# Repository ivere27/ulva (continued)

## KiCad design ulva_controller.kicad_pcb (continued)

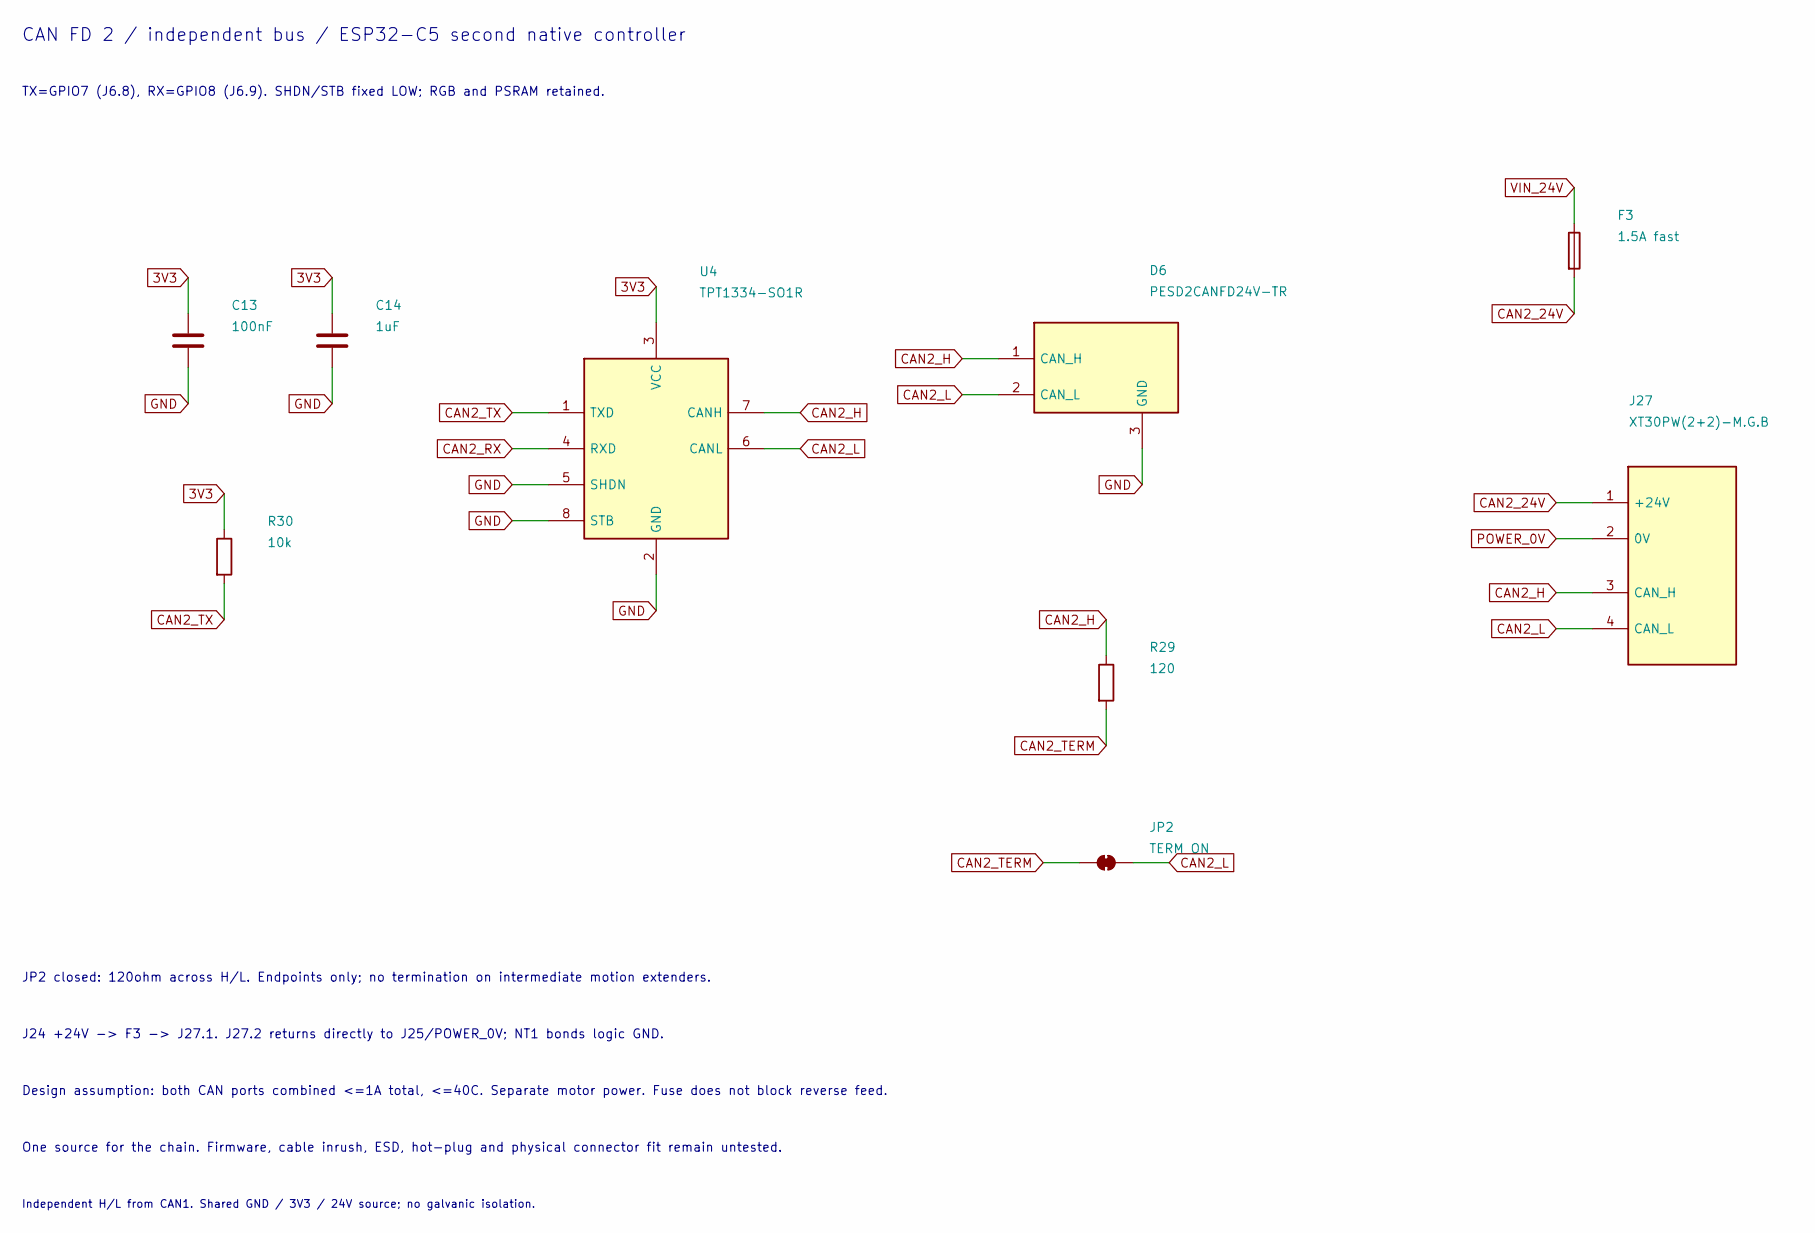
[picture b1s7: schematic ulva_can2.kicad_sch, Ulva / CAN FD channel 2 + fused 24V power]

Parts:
C13: 100nF; C_0603_1608Metric; MPN CC0603KRX7R9BB104; LCSC C14663
C14: 1uF; C_0603_1608Metric; MPN CL10A105KB8NNNC; LCSC C15849
D6: PESD2CANFD24V-TR; SOT-23; MPN PESD2CANFD24V-TR; LCSC C552486
F3: 1.5A fast; Fuse_Littelfuse_467_0603; MPN 046701.5NRHF; LCSC C187608
J27: XT30PW(2+2)-M.G.B; AMASS_XT30PW_2plus2_M_Horizontal; MPN XT30PW(2+2)-M.G.B; LCSC C19268030
JP2: TERM ON; SolderJumper-2_P1.3mm_Bridged_Pad1.0x1.5mm
R29: 120; R_1206_3216Metric; MPN 1206W4F1200T5E; LCSC C17909
R30: 10k; R_0603_1608Metric; MPN 0603WAF1002T5E; LCSC C25804
U4: TPT1334-SO1R; SOIC-8_3.9x4.9mm_P1.27mm; MPN TPT1334-SO1R; LCSC C44859616

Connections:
3V3: C13.1, C14.1, R30.1, U4.3 (VCC); also elsewhere on the board
CAN2_24V: F3.2, J27.1 (+24V)
CAN2_H: D6.1 (CAN_H), J27.3 (CAN_H), R29.1, U4.7 (CANH)
CAN2_L: D6.2 (CAN_L), J27.4 (CAN_L), JP2.2 (B), U4.6 (CANL)
CAN2_RX: U4.4 (RXD); also elsewhere on the board
CAN2_TERM: JP2.1 (A), R29.2
CAN2_TX: R30.2, U4.1 (TXD); also elsewhere on the board
GND: C13.2, C14.2, D6.3 (GND), U4.2 (GND), U4.5 (SHDN), U4.8 (STB); also elsewhere on the board
POWER_0V: J27.2 (0V); also elsewhere on the board
VIN_24V: F3.1; also elsewhere on the board

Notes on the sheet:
CAN FD 2 / independent bus / ESP32-C5 second native controller
TX=GPIO7 (J6.8), RX=GPIO8 (J6.9). SHDN/STB fixed LOW; RGB and PSRAM retained.
JP2 closed: 120ohm across H/L. Endpoints only; no termination on intermediate motion extenders.
J24 +24V -> F3 -> J27.1. J27.2 returns directly to J25/POWER_0V; NT1 bonds logic GND.
Design assumption: both CAN ports combined <=1A total, <=40C. Separate motor power. Fuse does not block reverse feed.
One source for the chain. Firmware, cable inrush, ESD, hot-plug and physical connector fit remain untested.
Independent H/L from CAN1. Shared GND / 3V3 / 24V source; no galvanic isolation.

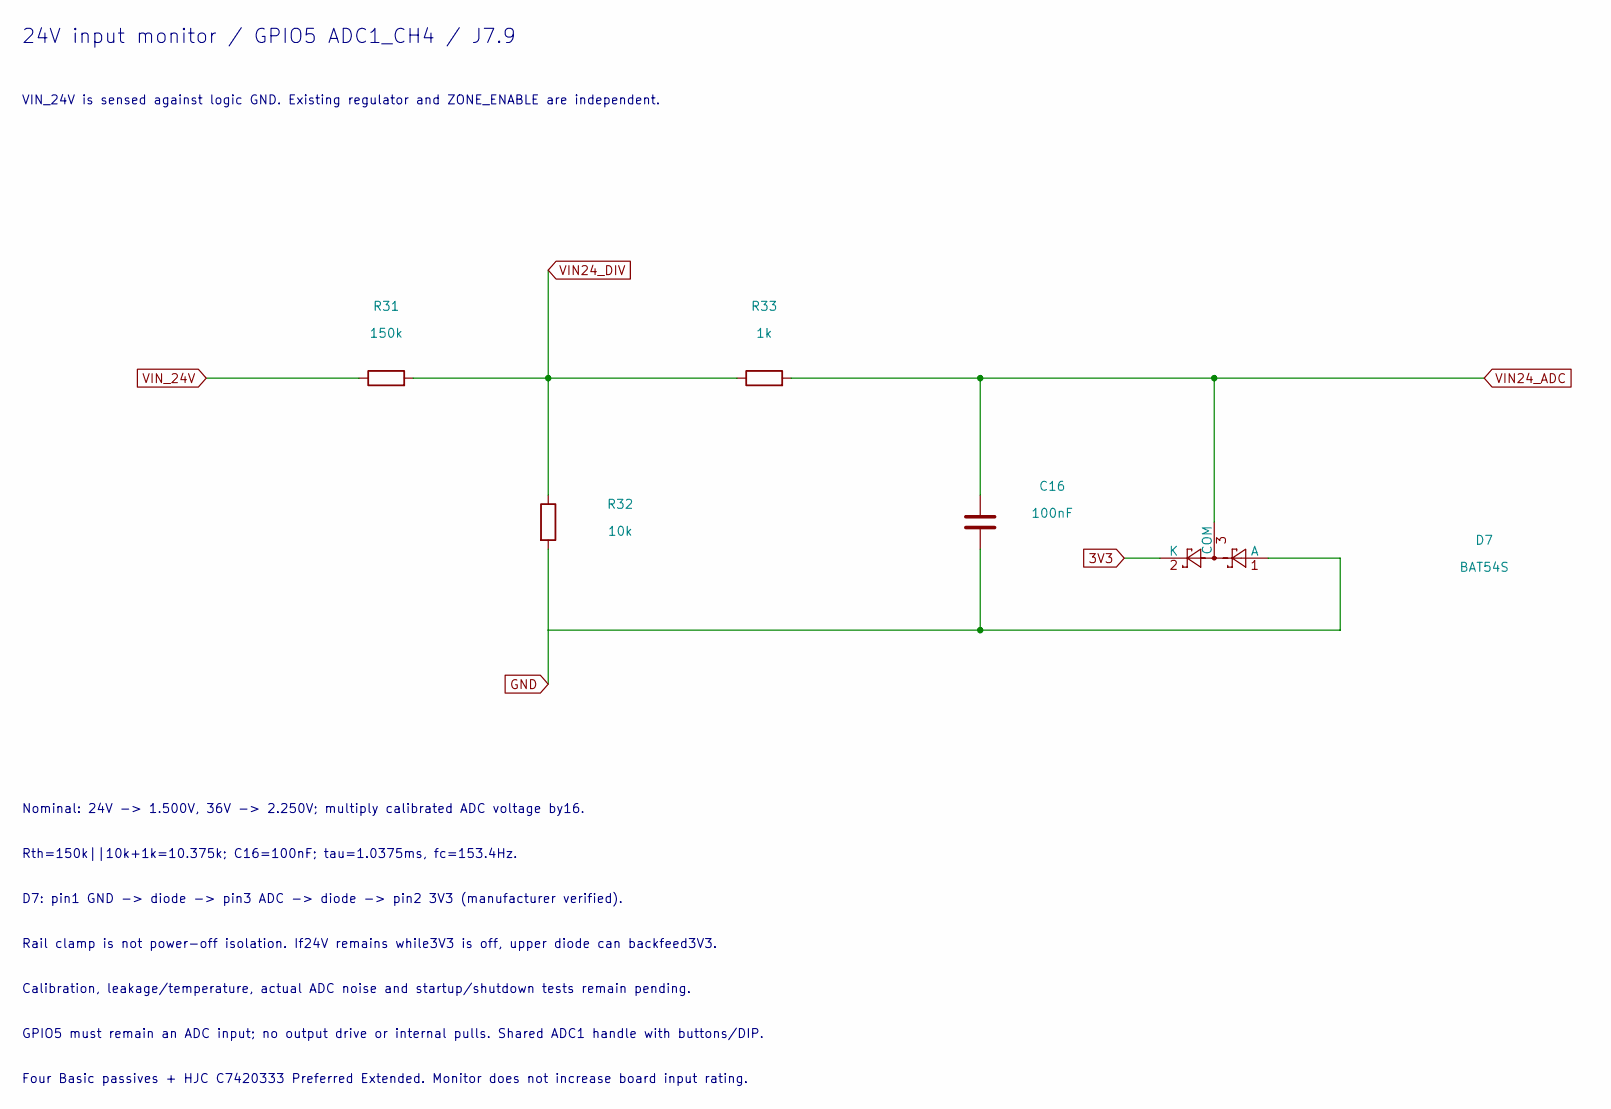
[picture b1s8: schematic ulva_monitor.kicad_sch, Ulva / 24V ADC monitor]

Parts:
C16: 100nF; C_0603_1608Metric; MPN CC0603KRX7R9BB104; LCSC C14663
D7: BAT54S; SOT-23; MPN BAT54S; LCSC C7420333
R31: 150k; R_0603_1608Metric; MPN 0603WAF1503T5E; LCSC C22807
R32: 10k; R_0603_1608Metric; MPN 0603WAF1002T5E; LCSC C25804
R33: 1k; R_0603_1608Metric; MPN 0603WAF1001T5E; LCSC C21190

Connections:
3V3: D7.2 (K); also elsewhere on the board
GND: C16.2, D7.1 (A), R32.2; also elsewhere on the board
VIN24_ADC: C16.1, D7.3 (COM), R33.2; also elsewhere on the board
VIN24_DIV: R31.2, R32.1, R33.1
VIN_24V: R31.1; also elsewhere on the board

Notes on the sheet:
24V input monitor / GPIO5 ADC1_CH4 / J7.9
VIN_24V is sensed against logic GND. Existing regulator and ZONE_ENABLE are independent.
Nominal: 24V -> 1.500V, 36V -> 2.250V; multiply calibrated ADC voltage by16.
Rth=150k||10k+1k=10.375k; C16=100nF; tau=1.0375ms, fc=153.4Hz.
D7: pin1 GND -> diode -> pin3 ADC -> diode -> pin2 3V3 (manufacturer verified).
Rail clamp is not power-off isolation. If24V remains while3V3 is off, upper diode can backfeed3V3.
Calibration, leakage/temperature, actual ADC noise and startup/shutdown tests remain pending.
GPIO5 must remain an ADC input; no output drive or internal pulls. Shared ADC1 handle with buttons/DIP.
Four Basic passives + HJC C7420333 Preferred Extended. Monitor does not increase board input rating.

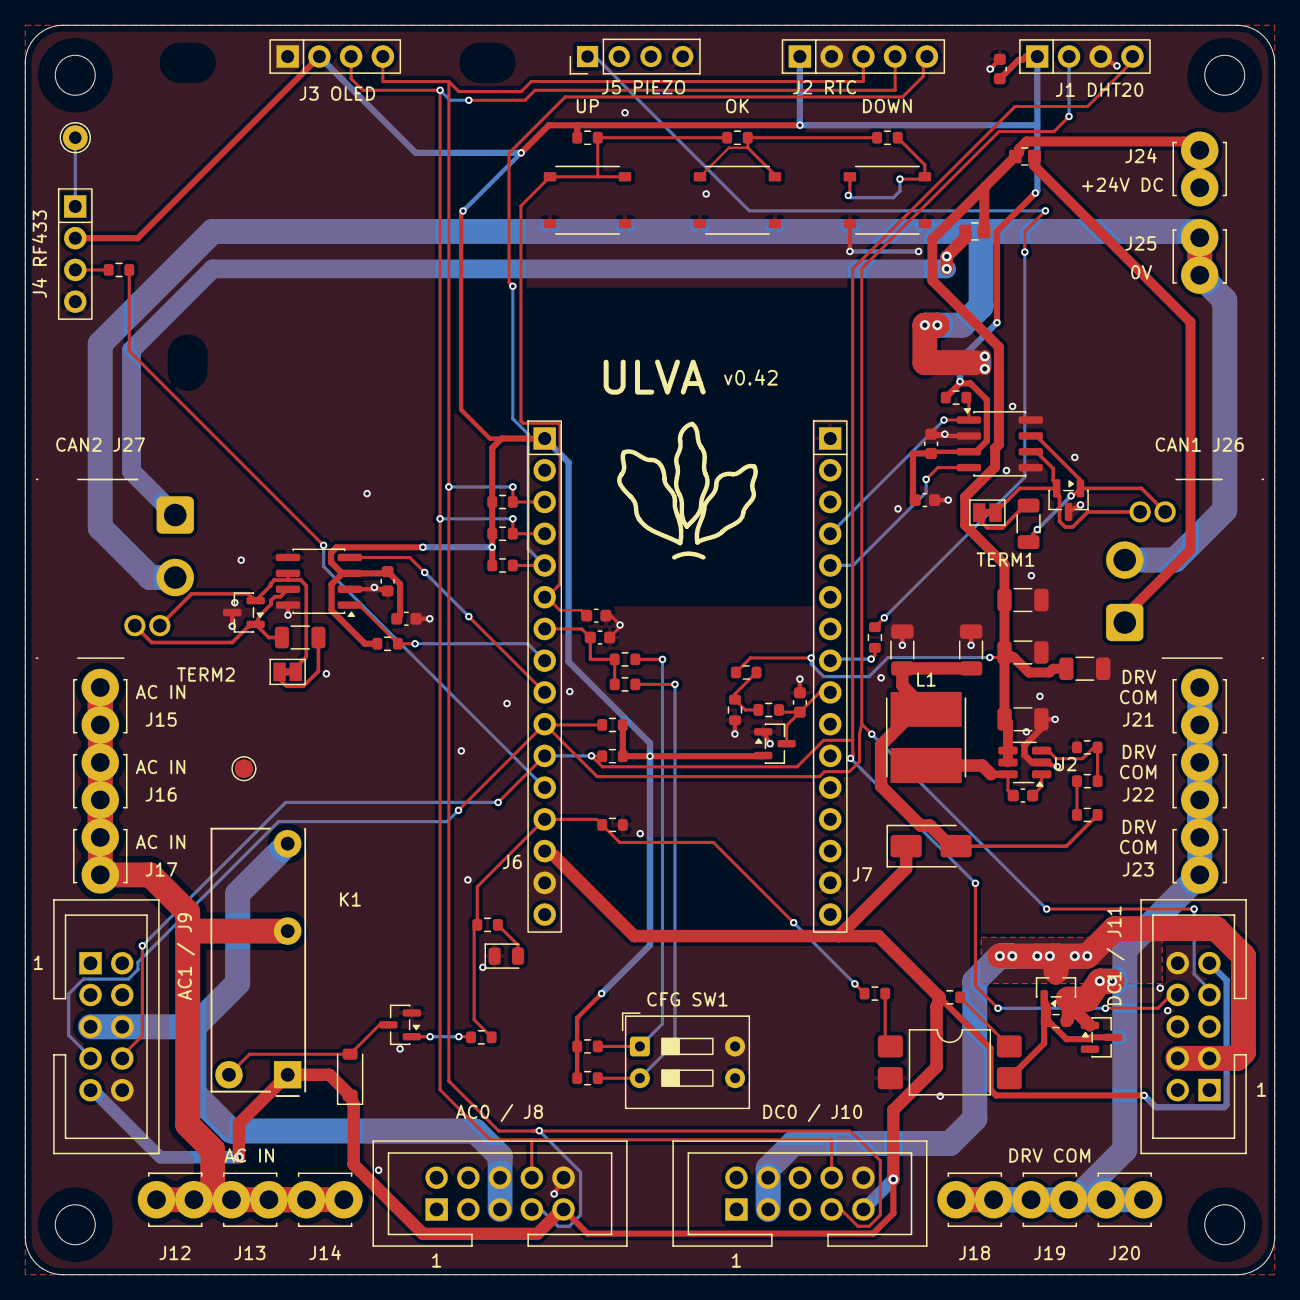
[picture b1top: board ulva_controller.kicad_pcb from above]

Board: 2 copper layers, 100.0 x 100.0 mm, 106 parts (0 on the bottom side), 51 nets.

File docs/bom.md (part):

# Bill of materials

The quantities below are for one **Ulva v0.42** carrier. The KiCad schematic
properties are the source of the part numbers; the PCB uses matching properties
and footprints. Plug-in modules, cables, mating connectors and mounting hardware
are additional items.

| Category | Quantity |
|---|---:|
| SMT parts tagged `JLC PCBA SMT` | 62 |
| Required manual SMT parts, U2 and L1 | 2 |
| Through-hole parts and antenna | 30 |
| PCB copper, holes, slots and test pad; no purchased component | 12 |
| **Total PCB footprints** | **106** |

There are **94 fitted parts** when fully populated. The tables record the design's
MPNs and LCSC numbers; they do not establish current stock, assembly availability
or library tier. A dash means that the corresponding sourcing field is not
recorded. See the [hardware reference](hardware.md) for wiring and power limits.

## SMT assembly candidates

These 62 parts carry the `JLC PCBA SMT` tag and are placed on the front side.
They form **26 part groups**, grouped by MPN, manufacturer, LCSC number and
footprint. The footprint column omits the KiCad library prefix.

| References | Qty | Value | Footprint | MPN | Manufacturer | LCSC |
|---|---:|---|---|---|---|---|
| C1, C5, C10, C12, C13, C15, C16 | 7 | 100nF; C5 explicitly marked 50V | `C_0603_1608Metric` | `CC0603KRX7R9BB104` | YAGEO | [C14663](https://www.lcsc.com/product-detail/C14663.html) |
| C3, C4, C8, C9 | 4 | 2.2uF / 50V | `C_1206_3216Metric` | `CL31B225KBHNNNE` | Samsung Electro-Mechanics | [C50254](https://www.lcsc.com/product-detail/C50254.html) |
| C6, C7 | 2 | 47uF / 10V | `C_1206_3216Metric` | `CL31A476MPHNNNE` | Samsung Electro-Mechanics | [C96123](https://www.lcsc.com/product-detail/C96123.html) |
| C11, C14 | 2 | 1uF | `C_0603_1608Metric` | `CL10A105KB8NNNC` | Samsung Electro-Mechanics | [C15849](https://www.lcsc.com/product-detail/C15849.html) |
| D1 | 1 | ZONE_ENABLE GREEN | `LED_0805_2012Metric` | `KT-0805G` | Hubei KENTO Elec | [C2297](https://www.lcsc.com/product-detail/C2297.html) |
| D2 | 1 | BZX84C8V2 | `SOT-23` | `BZX84C8V2` | hongjiacheng | [C22395522](https://www.lcsc.com/product-detail/C22395522.html) |
| D3 | 1 | 1N4148W | `D_SOD-123` | `1N4148W` | ST(Semtech) | [C81598](https://www.lcsc.com/product-detail/C81598.html) |
| D4 | 1 | SS34 | `D_SMA` | `SS34` | MDD | [C8678](https://www.lcsc.com/product-detail/C8678.html) |
| D5, D6 | 2 | PESD2CANFD24V-TR | `SOT-23` | `PESD2CANFD24V-TR` | Nexperia | [C552486](https://www.lcsc.com/product-detail/C552486.html) |
| D7 | 1 | BAT54S | `SOT-23` | `BAT54S` | hongjiacheng | [C7420333](https://www.lcsc.com/product-detail/C7420333.html) |
| F2, F3 | 2 | 1.5A fast | `Fuse_Littelfuse_467_0603` | `046701.5NRHF` | Littelfuse | [C187608](https://www.lcsc.com/product-detail/C187608.html) |
| Q1, Q2 | 2 | AO3400A | `SOT-23` | `AO3400A` | AOS | [C20917](https://www.lcsc.com/product-detail/C20917.html) |
| R1, R2, R3, R4, R13 | 5 | 4.7k | `R_0603_1608Metric` | `0603WAF4701T5E` | UNI-ROYAL | [C23162](https://www.lcsc.com/product-detail/C23162.html) |
| R5, R6, R11, R17, R26, R33 | 6 | 1k | `R_0603_1608Metric` | `0603WAF1001T5E` | UNI-ROYAL | [C21190](https://www.lcsc.com/product-detail/C21190.html) |
| R8, R12, R14, R15, R19, R23, R25, R27, R30, R32 | 10 | 10k | `R_0603_1608Metric` | `0603WAF1002T5E` | UNI-ROYAL | [C25804](https://www.lcsc.com/product-detail/C25804.html) |
| R16 | 1 | 2.2k | `R_0603_1608Metric` | `0603WAF2201T5E` | UNI-ROYAL | [C4190](https://www.lcsc.com/product-detail/C4190.html) |
| R18 | 1 | 330 | `R_0603_1608Metric` | `0603WAF3300T5E` | UNI-ROYAL | [C23138](https://www.lcsc.com/product-detail/C23138.html) |
| R20 | 1 | 47k | `R_0603_1608Metric` | `0603WAF4702T5E` | UNI-ROYAL | [C25819](https://www.lcsc.com/product-detail/C25819.html) |
| R21 | 1 | 51k | `R_0603_1608Metric` | `0603WAF5102T5E` | UNI-ROYAL | [C23196](https://www.lcsc.com/product-detail/C23196.html) |
| R22 | 1 | 2.7k | `R_0603_1608Metric` | `0603WAF2701T5E` | UNI-ROYAL | [C13167](https://www.lcsc.com/product-detail/C13167.html) |
| R24, R29 | 2 | 120 | `R_1206_3216Metric` | `1206W4F1200T5E` | UNI-ROYAL | [C17909](https://www.lcsc.com/product-detail/C17909.html) |
| R28 | 1 | 20k | `R_0603_1608Metric` | `0603WAF2002T5E` | UNI-ROYAL | [C4184](https://www.lcsc.com/product-detail/C4184.html) |
| R31 | 1 | 150k | `R_0603_1608Metric` | `0603WAF1503T5E` | UNI-ROYAL | [C22807](https://www.lcsc.com/product-detail/C22807.html) |
| SW2, SW3, SW4 | 3 | TS-1187A-B-A-B | `SW_XKB_TS-1187A_5.1x5.1mm` | `TS-1187A-B-A-B` | XKB Connection | [C318884](https://www.lcsc.com/product-detail/C318884.html) |
| U1 | 1 | LTV-817S-TA1-C | `SMDIP-4_W9.53mm` | `LTV-817S-TA1-C` | Lite-On | [C109227](https://www.lcsc.com/product-detail/C109227.html) |
| U3, U4 | 2 | TPT1334-SO1R | `SOIC-8_3.9x4.9mm_P1.27mm` | `TPT1334-SO1R` | 3PEAK | [C44859616](https://www.lcsc.com/product-detail/C44859616.html) |

## Manual assembly

U2 and L1 are required SMT parts tagged `Manual SMT`:

| References | Qty | Value | Footprint | MPN | Manufacturer | LCSC |
|---|---:|---|---|---|---|---|
| U2 | 1 | SY8301ABC | `SOT-23-6_Handsoldering` | `SY8301ABC` | Silergy | [C2927130](https://www.lcsc.com/product-detail/C2927130.html) |
| L1 | 1 | 4.7uH | `L_Sunlord_SWPA6045_6x6mm` | `SWPA6045S4R7MT` | Sunlord | [C78804](https://www.lcsc.com/product-detail/C78804.html) |

The following 30 parts use through-hole assembly. Only some carry an explicit
`Manual THT` tag; an empty assembly field does not make a part an SMT candidate.

| References | Qty | Use / value | Footprint | MPN | Manufacturer | LCSC |
|---|---:|---|---|---|---|---|
| J1, J3, J4 | 3 | DHT20, OLED and RF433 module sockets | `Samtec_SSW-104-01-G-S_1x04_P2.54mm` | `SSW-104-01-G-S` | — | — |
| J2 | 1 | DS3231 RTC socket | `Samtec_SSW-105-01-G-S_1x05_P2.54mm` | `SSW-105-01-G-S` | — | — |
| J5 | 1 | Passive piezo header; pins 1 and 4 used | `PinHeader_1x04_P2.54mm_Vertical` | — | — | — |
| J6, J7 | 2 | ESP32-C5-DevKitC-1 v1.2 sockets | `Samtec_SSW-116-01-G-S_1x16_P2.54mm` | `SSW-116-01-G-S` | — | — |
| J8, J9, J10, J11 | 4 | AC0, AC1, DC0 and DC1 expansion headers | `ZHOURI_DC3-2.54-10PAS_IDC_2x05_P2.54mm` | `DC3-2.54-10PAS` | — | [C2977596](https://www.lcsc.com/product-detail/C2977596.html) |
| J12, J13, J14, J15, J16, J17 | 6 | Six parallel AC2_IN terminals | `TerminalBlock_MetzConnect_360272_1x01_Horizontal_ScrewM2.6` | `360272` | — | — |
| J18, J19, J20, J21, J22, J23 | 6 | Six parallel DRIVER COM terminals | `TerminalBlock_MetzConnect_360272_1x01_Horizontal_ScrewM2.6` | `360272` | METZ CONNECT | — |
| J24, J25 | 2 | 24 V DC input positive / POWER_0V | `TerminalBlock_MetzConnect_360272_1x01_Horizontal_ScrewM2.6` | `360272` | METZ CONNECT | — |
| J26, J27 | 2 | CAN1 / CAN2 power and data | `AMASS_XT30PW_2plus2_M_Horizontal` | `XT30PW(2+2)-M.G.B` | AMASS | [C19268030](https://www.lcsc.com/product-detail/C19268030.html) |
| K1 | 1 | HF46F/5-HS1 relay | `Relay_SPST_Hongfa_HF46F_HS1` | `HF46F/5-HS1` | — | — |
| SW1 | 1 | 206-2ST configuration DIP switch | `SW_DIP_SPSTx02_Slide_9.78x7.26mm_W7.62mm_P2.54mm` | `206-2ST` | — | — |
| AE1 | 1 | 433 MHz wire / spring antenna | `TestPoint_THTPad_D2.0mm_Drill1.0mm` | — | — | — |

J1–J4 and J6/J7 specify Samtec SSW sockets; J12–J25 specify METZ CONNECT
360272 terminals; K1 specifies Hongfa HF46F/5-HS1 and SW1 specifies CTS 206-2ST.
Some manufacturer fields are empty in the source, as shown above. No alternate
LCSC part is approved by this table: matching pitch or a similar product name
alone does not establish footprint or electrical compatibility.

## Board features

These 12 footprints do not require purchased components:

| References | Qty | Feature | Footprint |
|---|---:|---|---|
| JP1, JP2 | 2 | Normally closed CAN termination copper bridges | `SolderJumper-2_P1.3mm_Bridged_Pad1.0x1.5mm` |
| NT1 | 1 | POWER_0V to GND copper bond | `NetTie-2_SMD_Pad2.0mm` |
| H1, H2, H3, H4 | 4 | M3 mounting holes | `MountingHole_3.2mm_M3` |
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
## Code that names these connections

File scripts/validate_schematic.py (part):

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value("C1", "100nF")

# Official ESP32-C5-DevKitC-1 v1.2 PSRAM header numbers, J1/J3.
# Bus0 uses LP-I2C fixed GPIO2/3; bus1 uses HP-I2C GPIO9/10. GPIO15 is unavailable with PSRAM.
mapping(
    "J6",
    {
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    "GPIO11 remains unused by the carrier for DevKit UART TX",
)
mapping("TP2", {1: "GND"})
mapping("J5", {1: "UI_PIEZO", 4: "GND"})
nc("J5", 2)
nc("J5", 3)
mapping("R26", {1: "UI_PIEZO_PWM", 2: "UI_PIEZO"})
value("R26", "1k")
require(
    components["J5"].findtext("footprint")
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        and components[rr].findtext("./fields/field[@name='LCSC']") == lcsc,
        rr + ": button ladder uses the specified 1% 0603 part",
    )
mapping("C15", {1: "UI_BUTTON_ADC", 2: "GND"})
value("C15", "100nF")
require(
    components["C15"].findtext("footprint") == "Capacitor_SMD:C_0603_1608Metric"
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        == "Basic",
        rr + ": specified 1% Basic resistor for the 24V monitor",
    )
mapping("C16", {1: "VIN24_ADC", 2: "GND"})
value("C16", "100nF")
require(
    components["C16"].findtext("footprint") == "Capacitor_SMD:C_0603_1608Metric"
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    and components["C16"].findtext("./fields/field[@name='LCSC']") == "C14663",
    "C16: X7R 50V storage/filter capacitor on the protected ADC node",
)
mapping("D7", {1: "GND", 2: "3V3", 3: "VIN24_ADC"})
value("D7", "BAT54S")
require(
    components["D7"].findtext("footprint") == "Package_TO_SOT_SMD:SOT-23"
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)

# Boot configuration: two independent SPST contacts, pairs 1-4 and 2-3.
mapping("SW1", {1: "CFG_SW1_N", 2: "CFG_SW2_N", 3: "GND", 4: "GND"})
config_symbol = components["SW1"].find("libsource")
require(
    config_symbol is not None
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    signal = f"CFG_SW{i}_N"
    mapping(pull, {1: "3V3", 2: signal})
    value(pull, "1k")
    mapping(weight, {1: signal, 2: "CFG_ADC"})
    value(weight, resistance)
    require(
        {pin for pin, code in net_by_pin.items() if names[code] == signal}
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            == expected_lcsc,
            rr + ": selected 1% 0603 resistor and matching BOM number",
        )
mapping("C12", {1: "CFG_ADC", 2: "GND"})
value("C12", "100nF")
require(
    components["C12"].findtext("footprint") == "Capacitor_SMD:C_0603_1608Metric"
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    "C12 uses the existing 100nF X7R 50V 0603 capacitor",
)
require(
    {pin for pin, code in net_by_pin.items() if names[code] == "CFG_ADC"}
    == {("J6", "7"), ("R27", "2"), ("R28", "2"), ("C12", "1")},
    "Only GPIO6 ADC1_CH5 reads the weighted DIP voltage; no direct switch or supply bypass",
)
require(
    not {"CFG0_N", "CFG1_N"} & set(names.values()),
    "DIP switches do not use separate GPIO input nets",
)
# RTC alarm and RF receiver have independent GPIOs; no selection links.
mapping("R8", {1: "3V3", 2: "RTC_INT_N"})
value("R8", "10k")
mapping("J2", {5: "RTC_INT_N"})
mapping("R11", {1: "RF433_DO", 2: "RF433_RX"})
value("R11", "1k")
for ref in ("J4", "AE1", "R11"):
    require(
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    )
require(
    not {"CFG2_N", "CFG3_N", "GPIO23_IN"} & set(names.values()),
    "No unsupported DIP or shared GPIO23 nets",
)
for name, expected in {
    "RTC_INT_N": {("J6", "5"), ("J2", "5"), ("R8", "2")},
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# netlist can verify the relay path, but not the installed source or fuse.
for ref in ("J15", "J12", "J16", "J17", "J13", "J14"):
    require(ref in components, f"Required AC screw terminal {ref} is missing")
    mapping(ref, {1: "AC2_IN"})
    require(
        {pin for rr, pin in net_by_pin if rr == ref} == {"1"},
        f"{ref} must have exactly one electrical terminal",
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        == "TerminalBlock_MetzConnect:TerminalBlock_MetzConnect_360272_1x01_Horizontal_ScrewM2.6",
        f"{ref} must use the selected single-position METZ CONNECT footprint",
    )
mapping("K1", {"A1": "EXP_5V", "A2": "AC_RELAY_LOW", "13": "AC2_IN", "14": "EACRET"})
value("K1", "HF46F/5-HS1")
require(
    components["K1"].findtext("footprint") == "Ulva:Relay_SPST_Hongfa_HF46F_HS1",
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    "K1 symbol must represent a normally-open SPST mechanical contact",
)
require(
    {pin for pin, code in net_by_pin.items() if names[code] == "AC2_IN"}
    == {(r, "1") for r in ("J15", "J12", "J16", "J17", "J13", "J14")} | {("K1", "13")},
    "Externally fused transformer wire2 reaches only J15.1/J12.1 and the K1 contact input",
)
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    ("J9", "I2C1", True),
    ("J11", "I2C1", False),
]:
    mapping(ref, {7: prefix + "_SDA", 8: prefix + "_SCL", 9: "EXP_5V", 10: "GND"})
    for p in (5, 6) if ac else (3, 4):
        mapping(ref, {p: "EACRET" if ac else "DC_ZONE_RETURN"})
    for p in (1, 2, 3, 4) if ac else (1, 2, 5, 6):
        nc(ref, p)
require(
    {pin for pin, code in net_by_pin.items() if names[code] == "EACRET"}
    == {("K1", "14"), ("J8", "5"), ("J8", "6"), ("J9", "5"), ("J9", "6")},
    "EACRET connects only K1 and AC return pins; no added ground bond",
)
require(
    {pin for pin, code in net_by_pin.items() if names[code] == "DC_ZONE_RETURN"}
    == {("Q2", "3"), ("J10", "3"), ("J10", "4"), ("J11", "3"), ("J11", "4")},
    "DC_ZONE_RETURN connects only Q2 drain and DC return pins; no added ground bond",
)
require(
    len({net_by_pin[("J8", "5")], net_by_pin[("J10", "3")], net_by_pin[("J8", "10")]})
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    and net_by_pin[("J8", "8")] != net_by_pin[("J9", "8")],
    "I2C0 and I2C1 (HP) expansion buses remain electrically separate",
)
# GPIO25 drives both fail-off paths. The AC MOSFET sinks the relay coil current;
# the optocoupler operates a board-5V-powered, single-MOSFET DC command-return cut.
mapping("Q1", {1: "AC_RELAY_GATE", 2: "GND", 3: "AC_RELAY_LOW"})
value("Q1", "AO3400A")
require(
    components["Q1"].findtext("footprint") == "Package_TO_SOT_SMD:SOT-23",
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    components["Q1"].findtext("./fields/field[@name='MPN']") == "AO3400A",
    "Q1 must use the specified logic-level coil driver",
)
mapping("R17", {1: "ZONE_ENABLE", 2: "AC_RELAY_GATE"})
value("R17", "1k")
mapping("R15", {1: "ZONE_ENABLE", 2: "GND"})
value("R15", "10k")
mapping("D3", {1: "EXP_5V", 2: "AC_RELAY_LOW"})
value("D3", "1N4148W")
require(
    components["D3"].findtext("footprint") == "Diode_SMD:D_SOD-123",
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    "D3 must use the specified coil-flyback diode",
)
require(
    {pin for pin, code in net_by_pin.items() if names[code] == "AC_RELAY_LOW"}
    == {("K1", "A2"), ("Q1", "3"), ("D3", "2")},
    "Relay coil low side reaches only the MOSFET drain and flyback diode anode",
)
require(
    {pin for pin, code in net_by_pin.items() if names[code] == "AC_RELAY_GATE"}
    == {("Q1", "1"), ("R17", "2")},
    "Relay gate reaches the shared R15 pull-down through R17",
)

for ref in ("J18", "J19", "J20", "J21", "J22", "J23"):
    mapping(ref, {1: "DC_DRIVER_COM"})
    require(
        components[ref].findtext("footprint")
        == components["J25"].findtext("footprint"),
        ref + " uses the selected COM terminal",
    )
mapping("J25", {1: "POWER_0V"})
require(
    {pin for rr, pin in net_by_pin if rr == "J25"} == {"1"},
    "J25 has only the supply-negative pin",
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    components["J25"].findtext("./fields/field[@name='MPN']") == "360272",
    "J25 uses METZ CONNECT 360272",
)
mapping("R18", {1: "ZONE_ENABLE", 2: "DC_LED_A"})
value("R18", "330")
mapping("U1", {1: "DC_LED_A", 2: "GND", 3: "DC_GATE", 4: "DC_OPTO_C"})
value("U1", "LTV-817S-TA1-C")
require(
    components["U1"].findtext("footprint") == "Package_DIP:SMDIP-4_W9.53mm",
    "U1 must use the selected gull-wing SMDIP-4 footprint",
)
mapping("Q2", {1: "DC_GATE", 2: "DC_DRIVER_COM", 3: "DC_ZONE_RETURN"})
value("Q2", "AO3400A")
require(
    components["Q2"].findtext("footprint") == "Package_TO_SOT_SMD:SOT-23",
    "Q2 must use the selected AO3400A SOT-23 footprint",
)
mapping("D2", {1: "DC_DRIVER_COM", 3: "DC_GATE"})
nc("D2", 2)
value("D2", "BZX84C8V2")
for field, expected in {
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        components["D2"].findtext(f"./fields/field[@name='{field}']") == expected,
        f"D2 {field} must match the selected C22395522, independently of Q2",
    )
mapping("R19", {1: "EXP_5V", 2: "DC_OPTO_C"})
value("R19", "10k")
mapping("R20", {1: "DC_GATE", 2: "DC_DRIVER_COM"})
value("R20", "47k")
require(
    {pin for pin, code in net_by_pin.items() if names[code] == "DC_DRIVER_COM"}
    == {(r, "1") for r in ("J18", "J19", "J20", "J21", "J22", "J23")}
    | {("Q2", "2"), ("R20", "2"), ("D2", "1")},
    "DRIVER COM reaches only six command terminals, Q2 source and gate protection",
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        },
    )
    value(u, "TPT1334-SO1R")
    mapping(j, {1: n("24V"), 2: "POWER_0V", 3: n("H"), 4: n("L")})
    mapping(d, {1: n("H"), 2: n("L"), 3: "GND"})
    value(d, "PESD2CANFD24V-TR")
    mapping(f, {1: "VIN_24V", 2: n("24V")})
    value(f, "1.5A fast")
    mapping(term, {1: n("H"), 2: n("TERM")})
    value(term, "120")
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]
mapping("J24", {1: vin})
value("J24", "24V DC +")
mapping("NT1", {1: "POWER_0V", 2: "GND"})
require(
    components["NT1"].findtext("footprint") == "NetTie:NetTie-2_SMD_Pad2.0mm",
    "NT1 uses a copper-connected net-tie footprint, not an uninstalled jumper",
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value("U2", "SY8301ABC")
mapping("L1", {1: lx, 2: raw})
value("L1", "4.7uH")
mapping("D4", {1: "EXP_5V", 2: raw})
value("D4", "SS34")
for ref in ("C3", "C4", "C8", "C9"):
    mapping(ref, {1: vin, 2: "GND"})
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
# Direct expander I2C: logic stays pulled up to 3V3 while EVIN stays EXP_5V.
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
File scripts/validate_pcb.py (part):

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)
require(
    fps["R26"].GetValue() == "1k" and distance(at("R26", 1), at("J7", 8)) < 5,
    "Piezo series input within 5 mm of dedicated GPIO4; RGB27 has no carrier trace",
)
require(
    fps["SW1"].GetFPID().GetLibItemName()
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    require(fps[ref].GetValue() == val, ref + ": weighted ADC value")
require(
    distance(at("C12", 1), at("J6", 7)) < 10,
    "ADC filter capacitor within 10 mm of GPIO6",
)
for ref in ["R27", "R28"]:
    require(
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for ref, val in [("R12", "10k"), ("R13", "4.7k"), ("R14", "10k"), ("C15", "100nF")]:
    require(fps[ref].GetValue() == val, ref + ": button ADC ladder value")
require(
    distance(at("C15", 1), at("J6", 6)) < 5, "Button ADC filter within 5 mm of GPIO1"
)
for ref, val in [
    ("R31", "150k"),
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        ref + ": 24V monitor part on top assembly layer",
    )
require(
    pad("J7", 9).GetNetname() == "VIN24_ADC" and pad("J7", 9).GetPinType() == "input",
    "GPIO5 is connected and configured as an ADC input",
)
require(
    distance(at("C16", 1), at("J7", 9)) < 5,
    "24V ADC storage/filter capacitor within 5 mm of GPIO5",
)
require(
    distance(at("D7", 3), at("J7", 9)) < 6,
    "24V ADC BAT54S junction within 6 mm of GPIO5",
)
require(
    {q.GetNumber(): q.GetNetname() for q in fps["D7"].Pads()}
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    len(heat) == 2
    and {z.GetLayer() for z in heat} == {p.F_Cu, p.B_Cu}
    and all(
        z.GetNetname() == "DC_ZONE_RETURN" and z.GetFilledArea() / 1e12 >= 35
        for z in heat
    ),
    "Q2 drain heat copper >=35 mm2 per layer",
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}.items():
    require(all(pad(ref, number).GetNetname() == net for number, net in pins.items()), ref + ": rear pin legend matches PCB nets")
for ref, bus in [("J8", 0), ("J9", 1), ("J10", 0), ("J11", 1)]:
    pins = {"7": f"I2C{bus}_SDA", "8": f"I2C{bus}_SCL", "9": "EXP_5V", "10": "GND"}
    require(all(pad(ref, number).GetNetname() == net for number, net in pins.items()), ref + ": IDC legend matches bus and power pins")

icons = [g for g in b.Groups() if g.GetName().startswith("ULVA sea lettuce icon")]
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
